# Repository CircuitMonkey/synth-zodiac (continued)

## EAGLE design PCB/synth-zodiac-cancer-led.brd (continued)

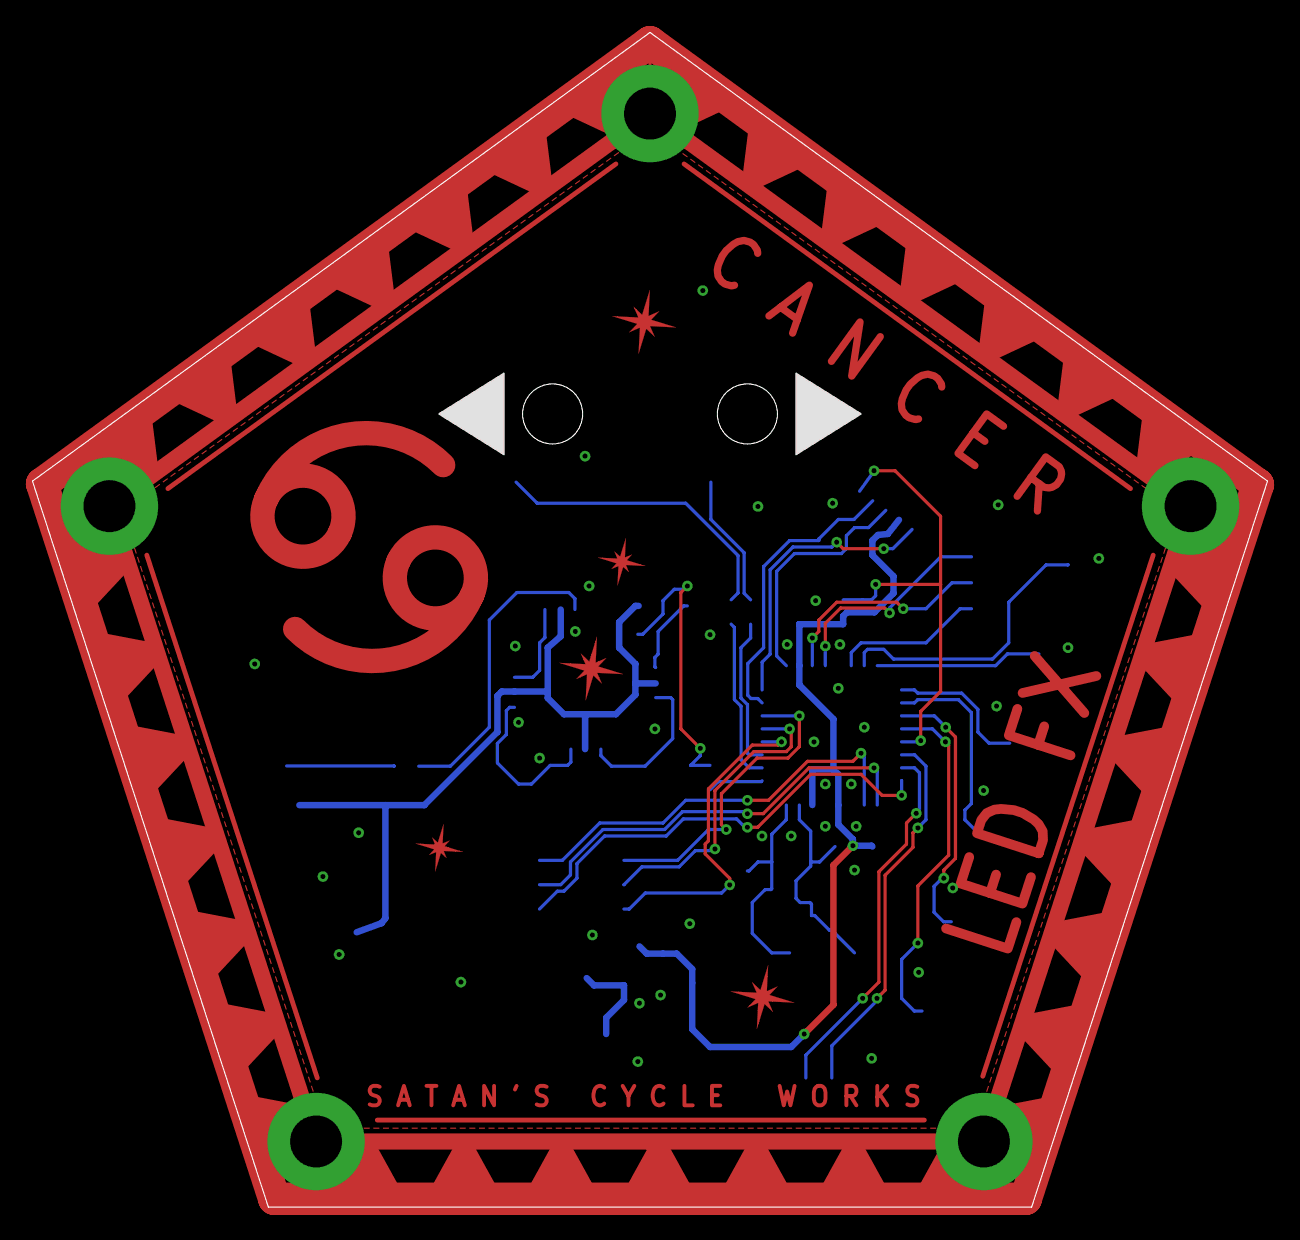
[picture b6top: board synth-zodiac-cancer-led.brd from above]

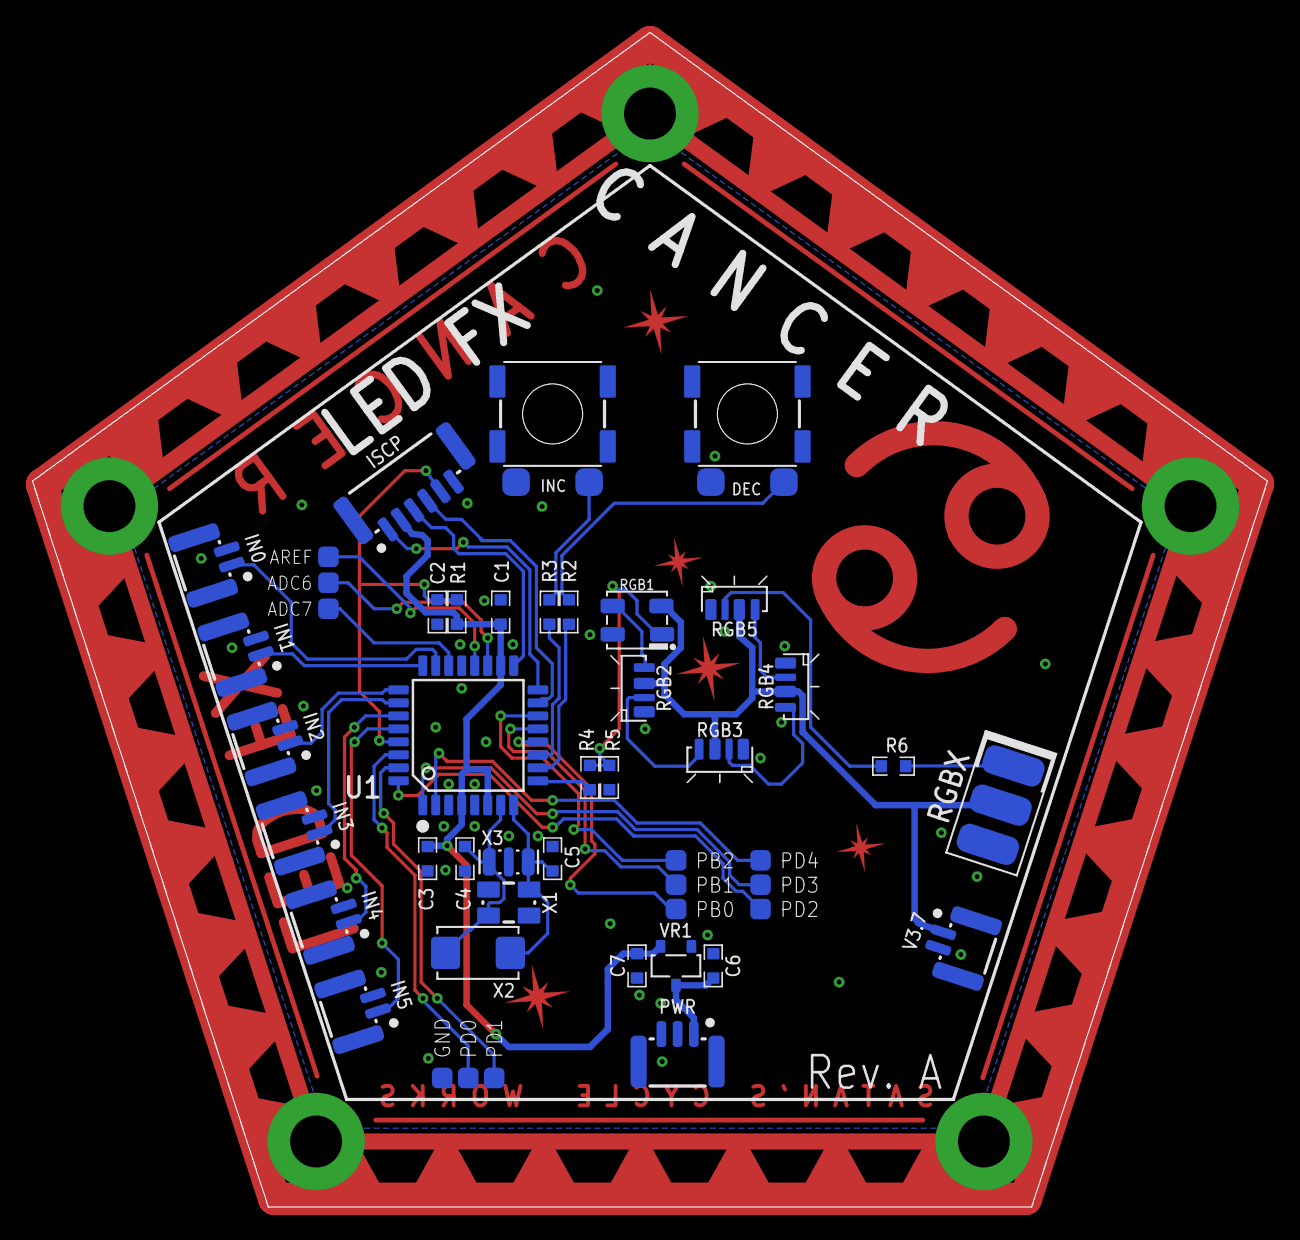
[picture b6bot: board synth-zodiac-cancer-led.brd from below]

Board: 2 copper layers, 76.1 x 72.4 mm, 50 parts (45 on the bottom side), 39 nets.

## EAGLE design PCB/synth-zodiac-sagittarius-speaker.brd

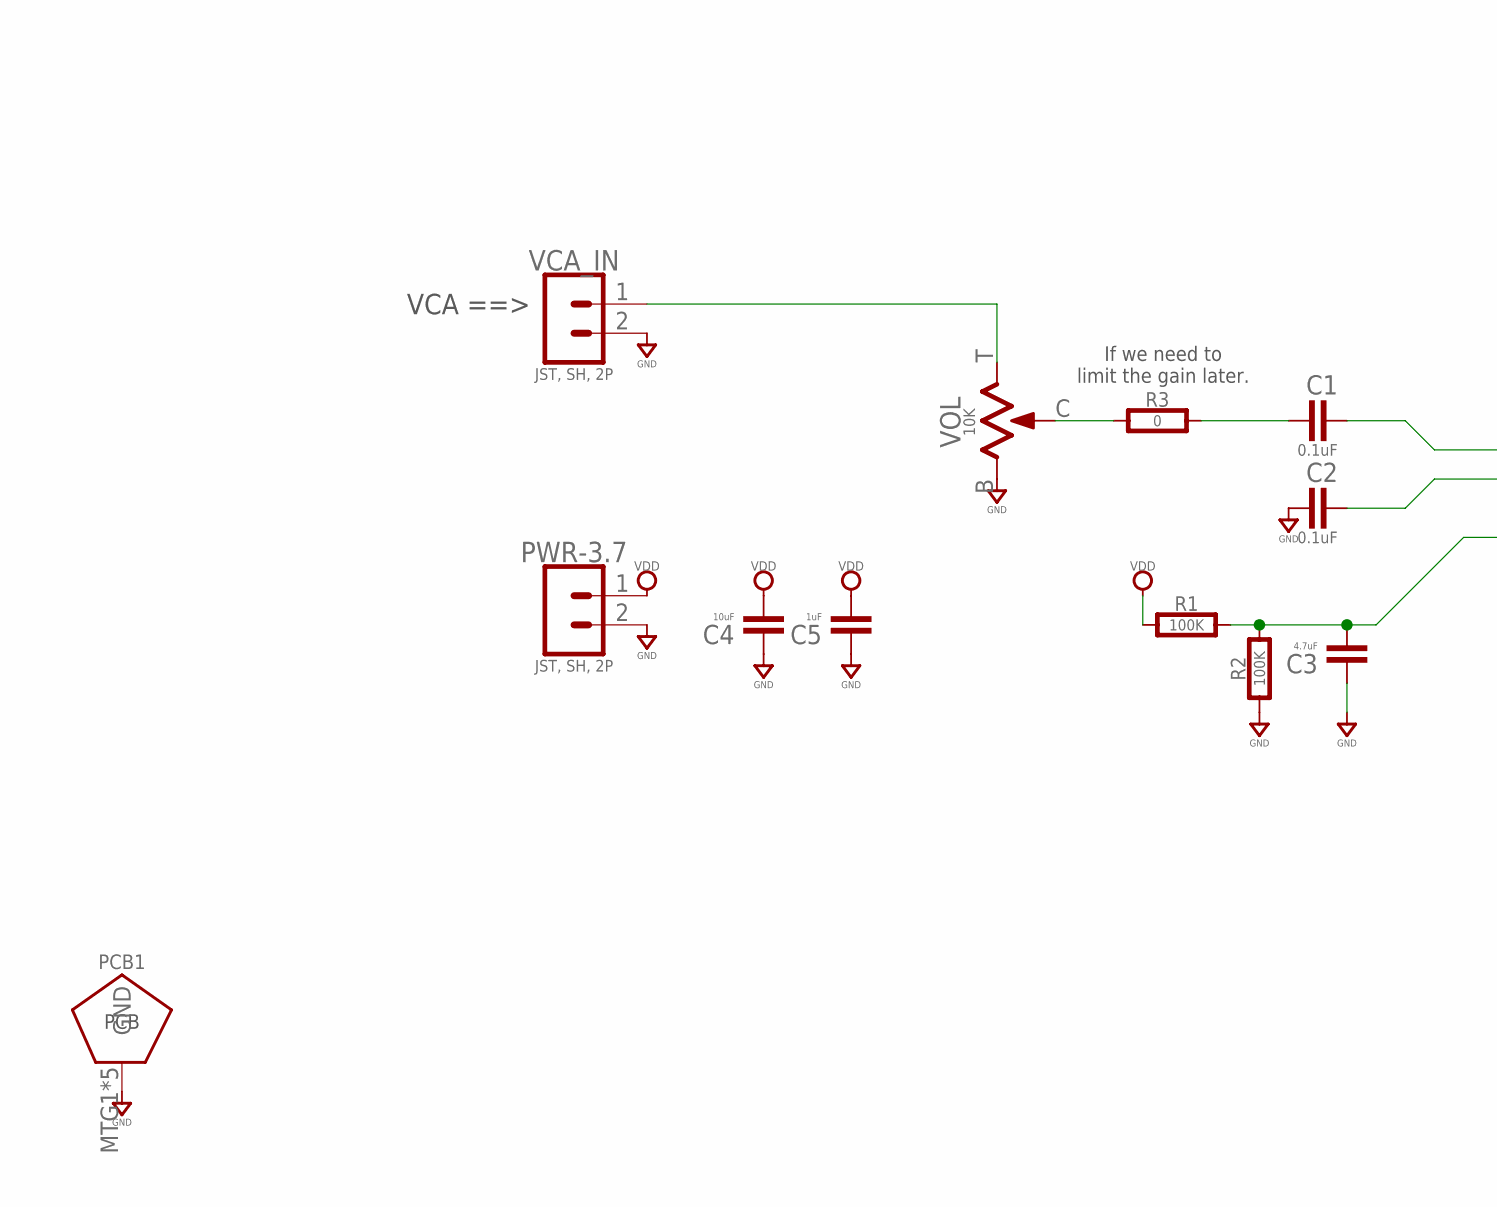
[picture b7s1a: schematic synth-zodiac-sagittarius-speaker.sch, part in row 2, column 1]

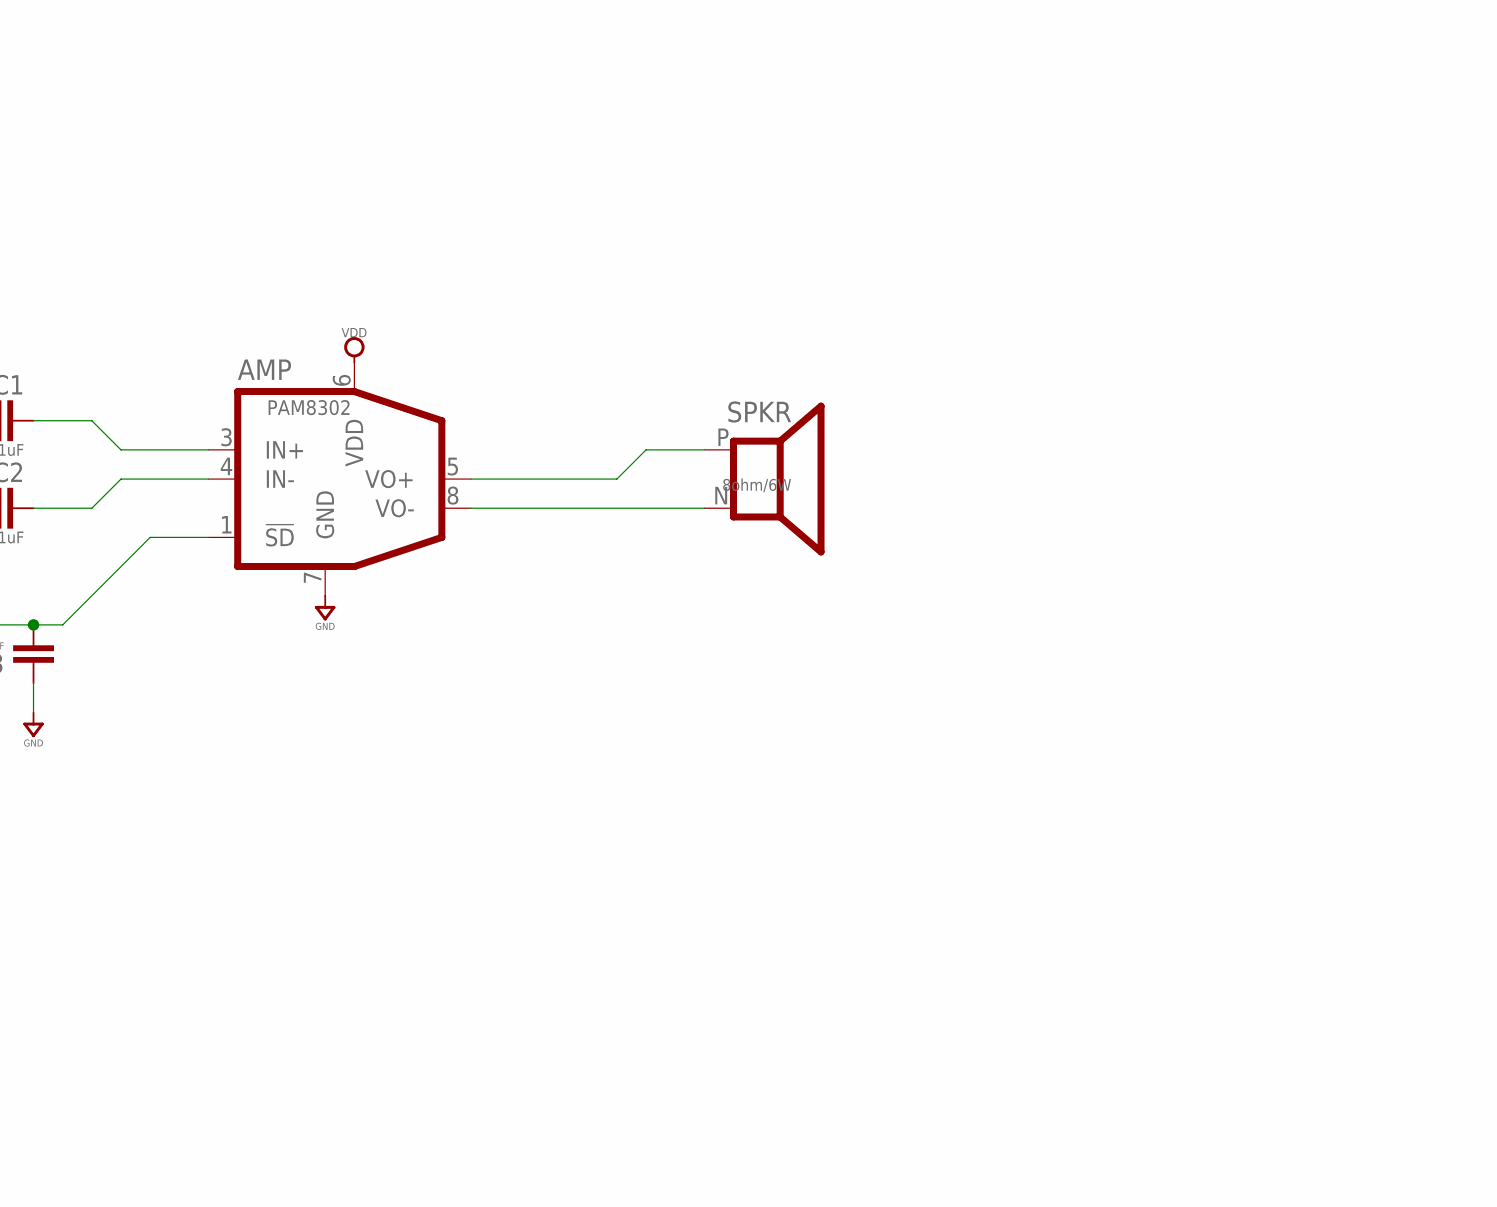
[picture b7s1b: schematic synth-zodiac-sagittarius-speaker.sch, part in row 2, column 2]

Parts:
AMP: PAM8302; U-DFN3030-8
C1, C2: 0.1uF; 0603-CAP
C3: 4.7uF; 0603-CAP
C4: 10uF; 0603-CAP
C5: 1uF; 0603-CAP
PCB1: PCB FAB; PENTAGON-40MM-RAD
PWR-3.7: JST, SH, 2P; BM02B-SRSS-TB
R1, R2: 100K; 0603-RES
R3: 0; 0603-RES
SPKR: 8ohm/6W; SPKR-40X30
VCA_IN: JST, SH, 2P; BM02B-SRSS-TB
VOL: 10K; POT-RV9110

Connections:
GND: AMP.7 (GND), C2.1, C3.1, C4.1, C5.1, PCB1.MTG1, PCB1.MTG2, PCB1.MTG3, PCB1.MTG4, PCB1.MTG5, PWR-3.7.2, R2.1, VCA_IN.2, VOL.B (1)
unnamed: AMP.3 (IN+), C1.2
unnamed: AMP.4 (IN-), C2.2
unnamed: VCA_IN.1, VOL.T (3)
unnamed: C1.1, R3.2
unnamed: AMP.1 (!SD), C3.2, R1.2, R2.2
unnamed: AMP.5 (VO+), SPKR.P (+)
unnamed: AMP.8 (VO-), SPKR.N (-)
unnamed: R3.1, VOL.C (2)
VDD: AMP.6 (VDD), C4.2, C5.2, PWR-3.7.1, R1.1

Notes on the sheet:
VCA ==>
If we need to limit the gain later.
Amp & Speaker
Zodiac Synth
Sagittarius
SATAN'S CYCLE WORKS

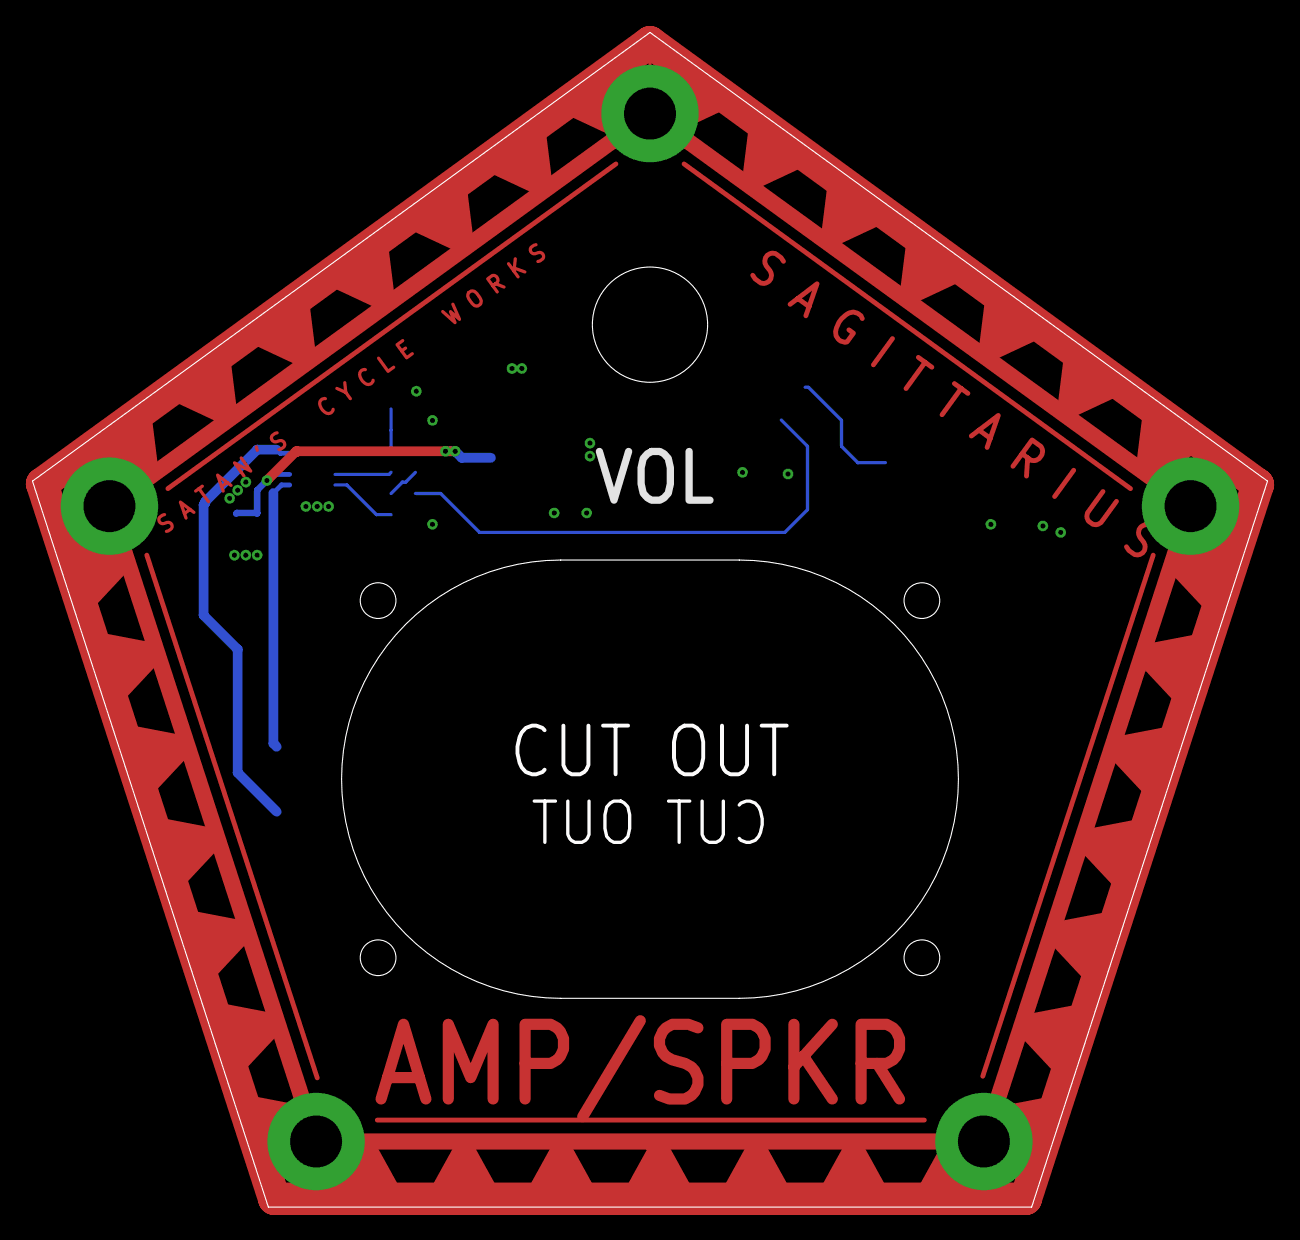
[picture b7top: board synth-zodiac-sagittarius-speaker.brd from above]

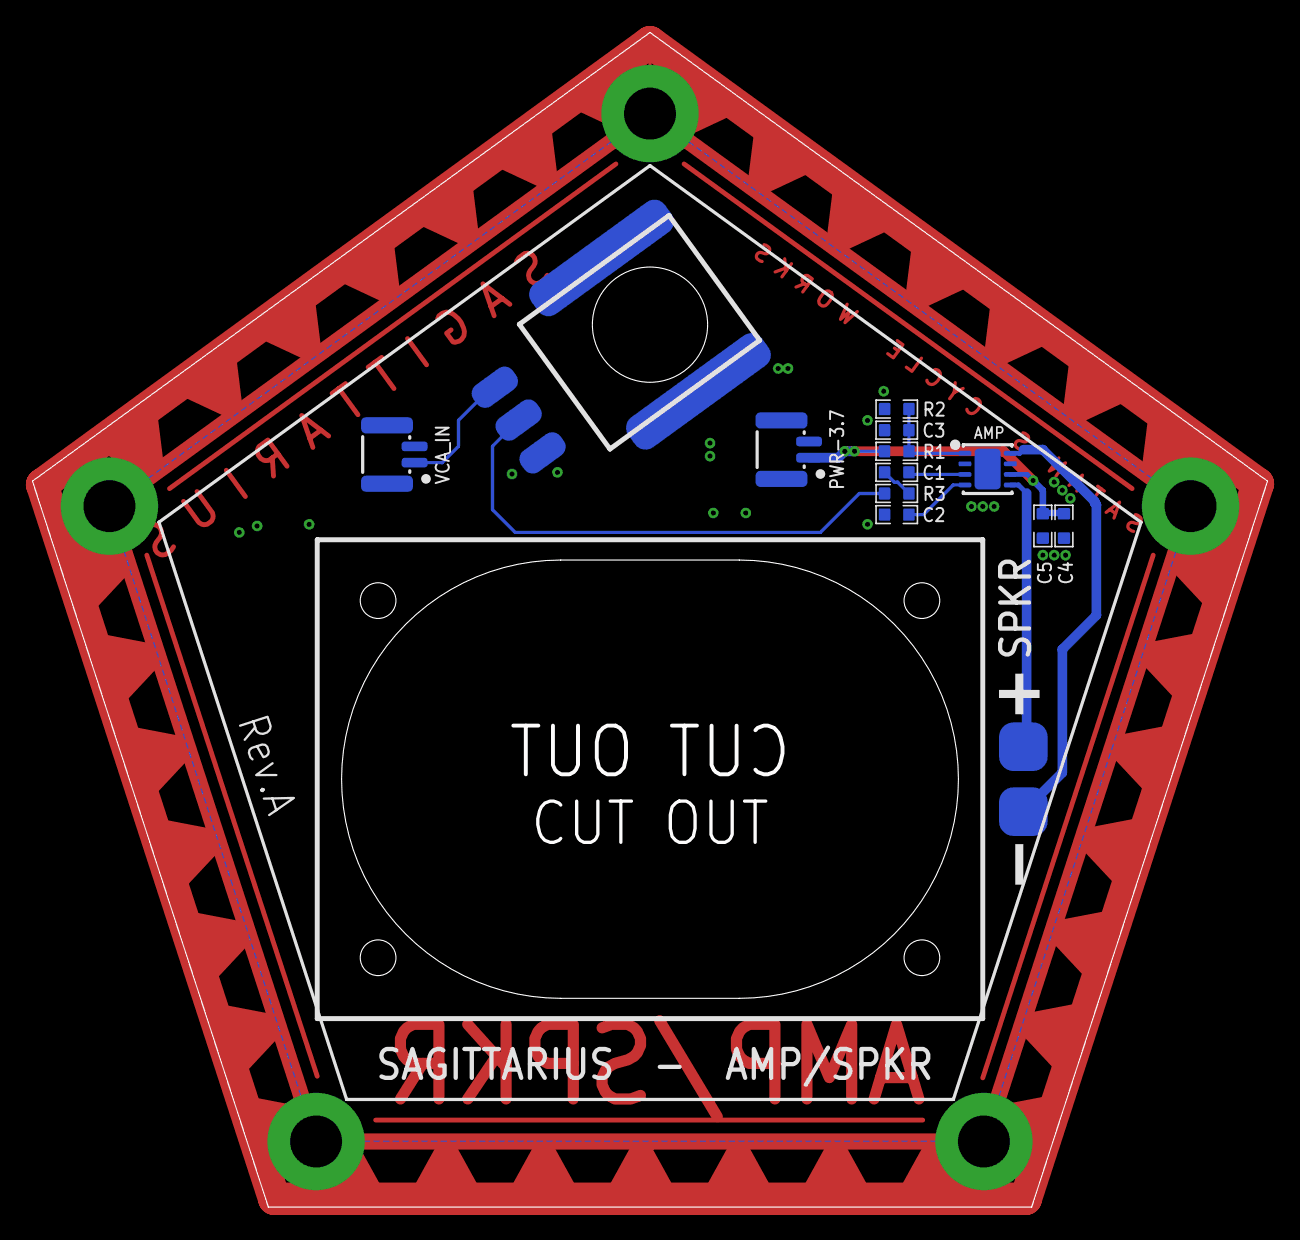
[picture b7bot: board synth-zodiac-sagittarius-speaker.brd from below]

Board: 2 copper layers, 76.1 x 72.4 mm, 14 parts (13 on the bottom side), 10 nets.

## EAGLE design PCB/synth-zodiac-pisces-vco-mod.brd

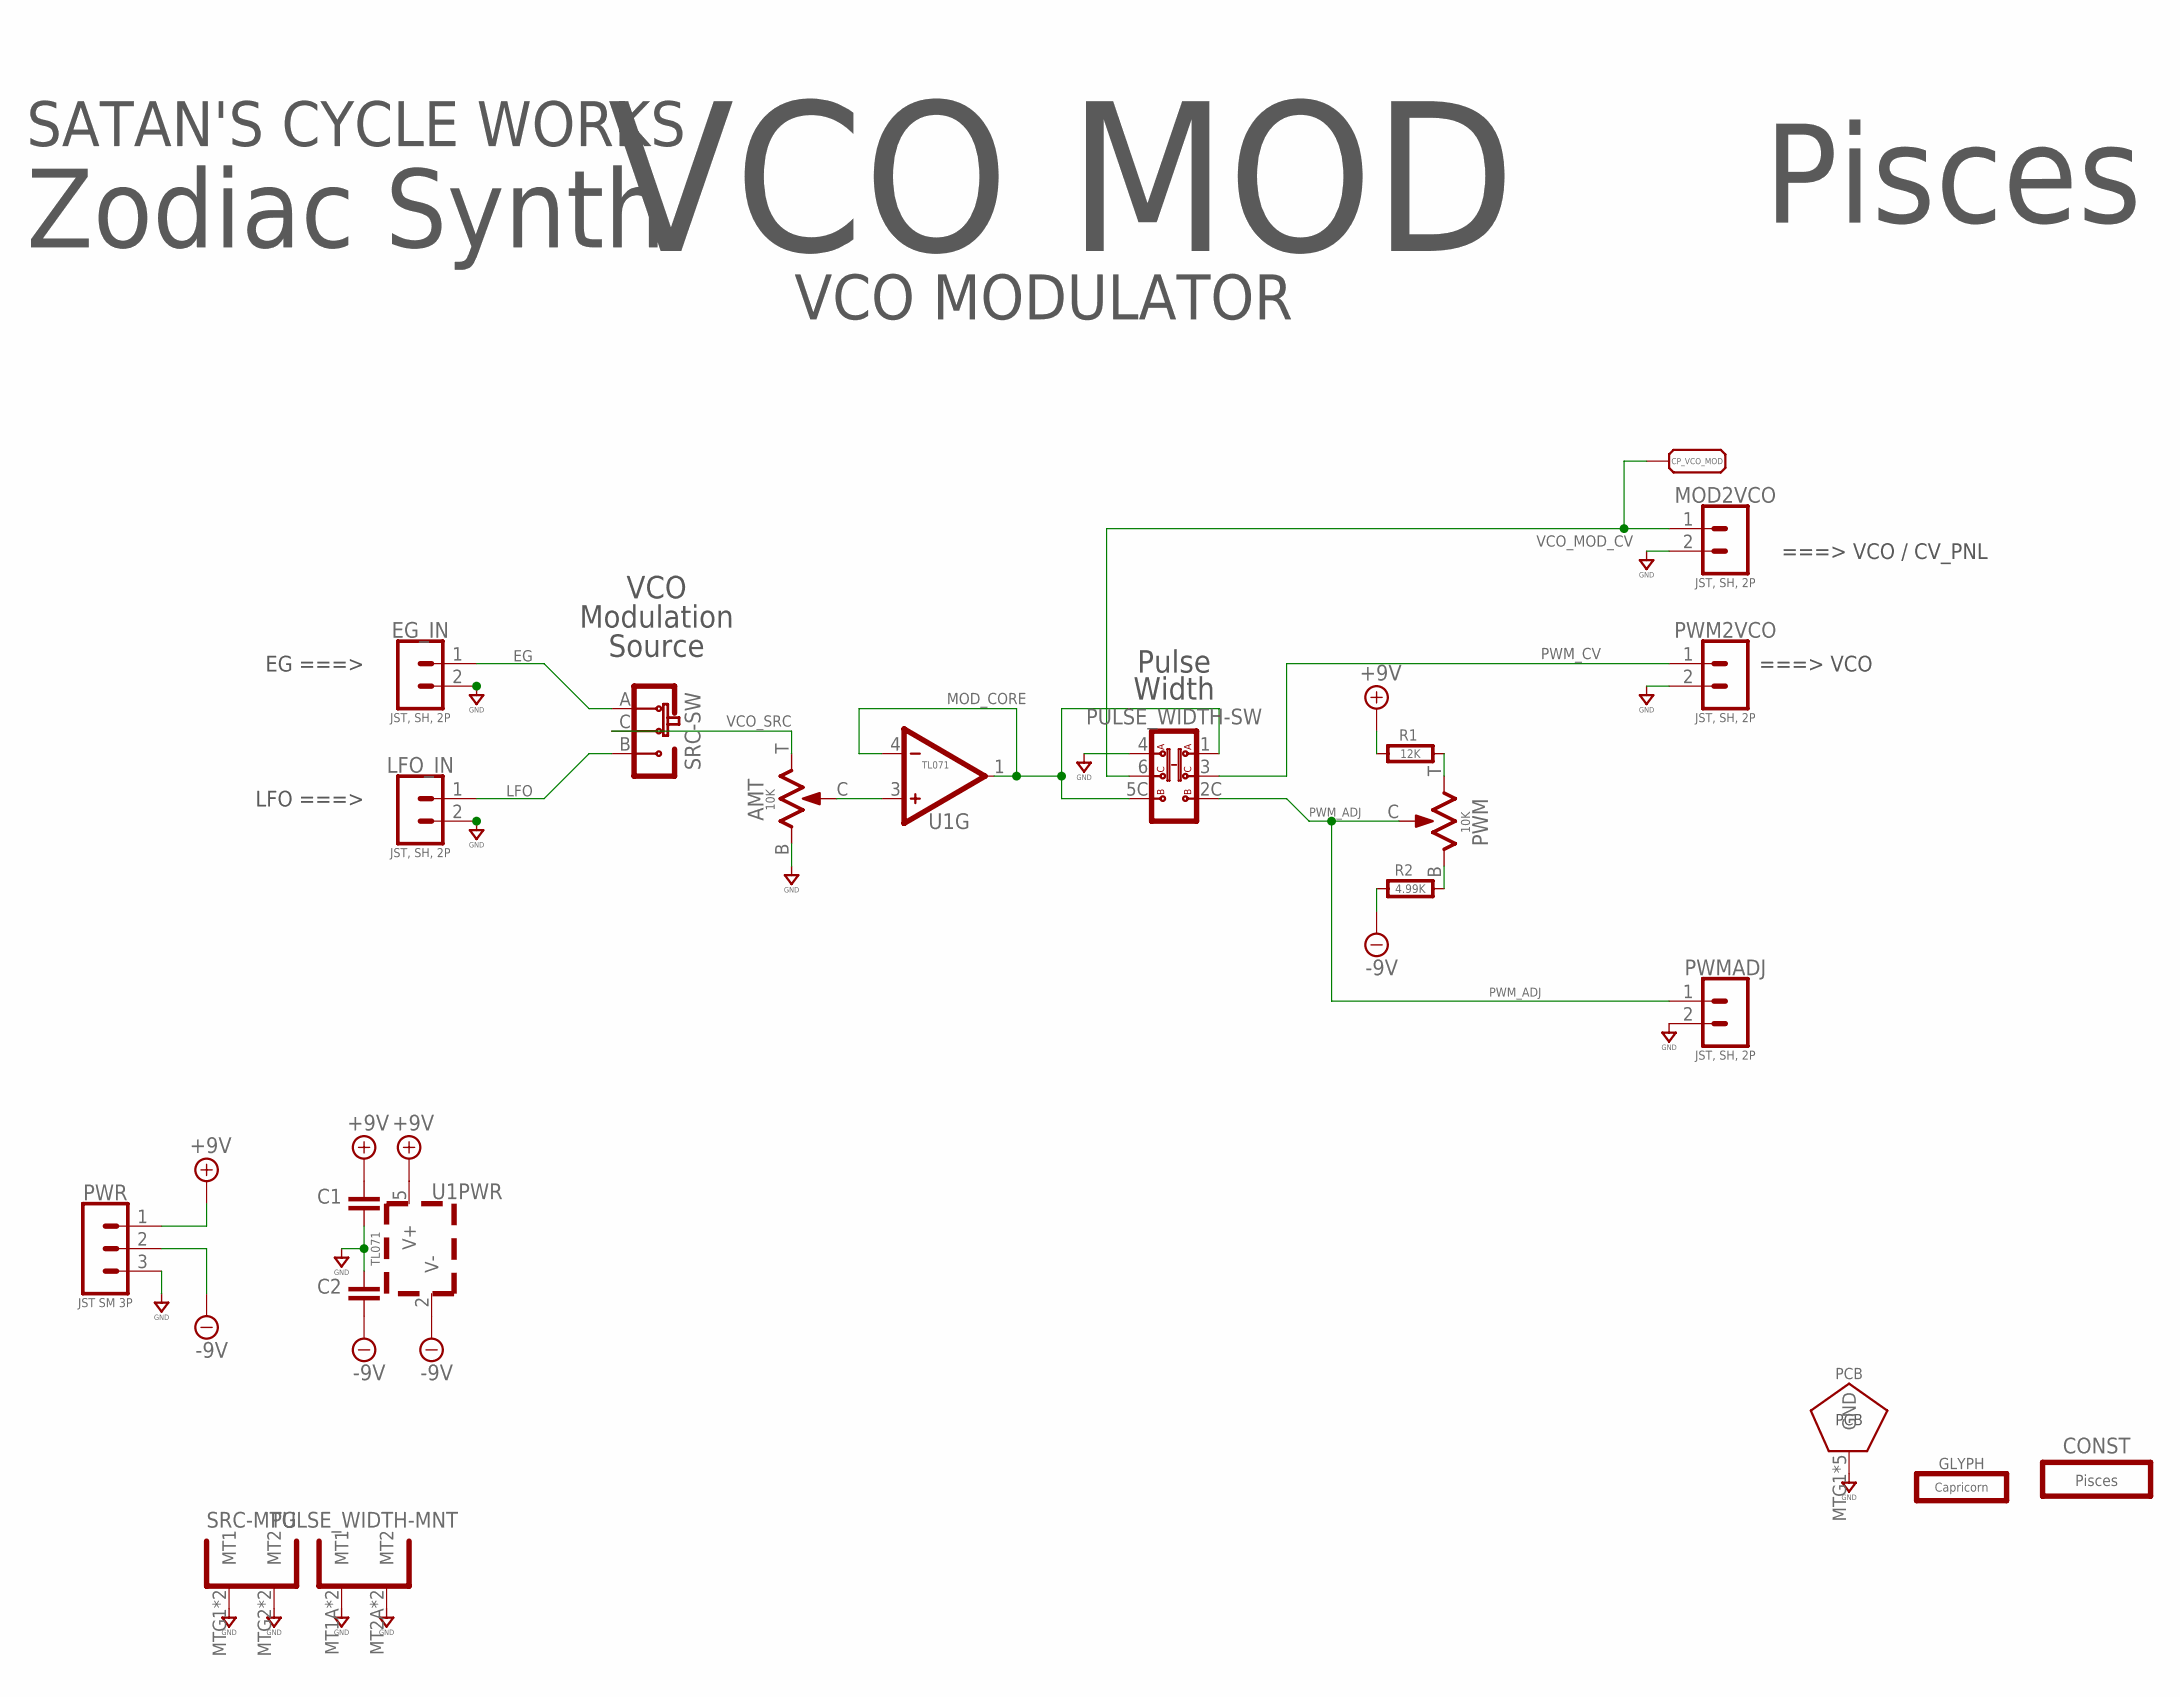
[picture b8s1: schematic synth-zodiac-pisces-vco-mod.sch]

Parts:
AMT: 10K; POT-RV9110
C1, C2: 0.1uF; 0603-CAP
CONST: Pisces; PISCES-CONST
CP_VCO_MOD: PADSMD-070X070; SMD-070MIL
EG_IN: JST, SH, 2P; BM02B-SRSS-TB
GLYPH: Capricorn; CAPRICORN-GLYPH
LFO_IN: JST, SH, 2P; BM02B-SRSS-TB
MOD2VCO: JST, SH, 2P; BM02B-SRSS-TB
PCB: PCB FAB; PENTAGON-40MM-RAD
PULSE_WIDTH: Switch, DPDT; CK_OS202013MT5-PNL-SMT-2
PWM: 10K; POT-RV9110
PWM2VCO: JST, SH, 2P; BM02B-SRSS-TB
PWMADJ: JST, SH, 2P; BM02B-SRSS-TB
PWR: JST SM 3P; BM03B-SRSS-TB
R1: 12K; 0603-RES
R2: 4.99K; 0603-RES
SRC: SLIDE-SPDT-MNTSS-12-F45-TH-PCB-2; SS-12-F45-PNL-SMT-2
U1: TL071; SOT-23-5

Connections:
+9V: C1.1, PWR.1, R1.1, U1.5 (V+)
-9V: C2.2, PWR.2, R2.2, U1.2 (V-)
EG: EG_IN.1, SRC.A
GND: AMT.B (1), C1.2, C2.1, EG_IN.2, LFO_IN.2, MOD2VCO.2, PCB.MTG1, PCB.MTG2, PCB.MTG3, PCB.MTG4, PCB.MTG5, PULSE_WIDTH.4 (2A), PULSE_WIDTH.MT1A (MT1), PULSE_WIDTH.MT2A (MT2), PULSE_WIDTH.MT3A (MT1), PULSE_WIDTH.MT4A (MT2), PWM2VCO.2, PWMADJ.2, PWR.3, SRC.MTG1 (MT1), SRC.MTG2 (MT2), SRC.MTG3 (MT1), SRC.MTG4 (MT2)
LFO: LFO_IN.1, SRC.B
MOD_CORE: PULSE_WIDTH.1 (1A), PULSE_WIDTH.5C (2B), U1.1 (OUT), U1.4 (-)
unnamed: AMT.C (2), U1.3 (+)
unnamed: PWM.B (1), R2.1
unnamed: PWM.T (3), R1.2
PWM_ADJ: PULSE_WIDTH.2C (1B), PWM.C (2), PWMADJ.1
PWM_CV: PULSE_WIDTH.3 (1C), PWM2VCO.1
VCO_MOD_CV: CP_VCO_MOD.1, MOD2VCO.1, PULSE_WIDTH.6 (2C)
VCO_SRC: AMT.T (3), SRC.C

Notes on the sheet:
VCO MODULATOR
VCO Modulation Source
Pulse Width
EG ===>
LFO ===>
===> VCO / CV_PNL
===> VCO
VCO MOD
Zodiac Synth
Pisces
SATAN'S CYCLE WORKS

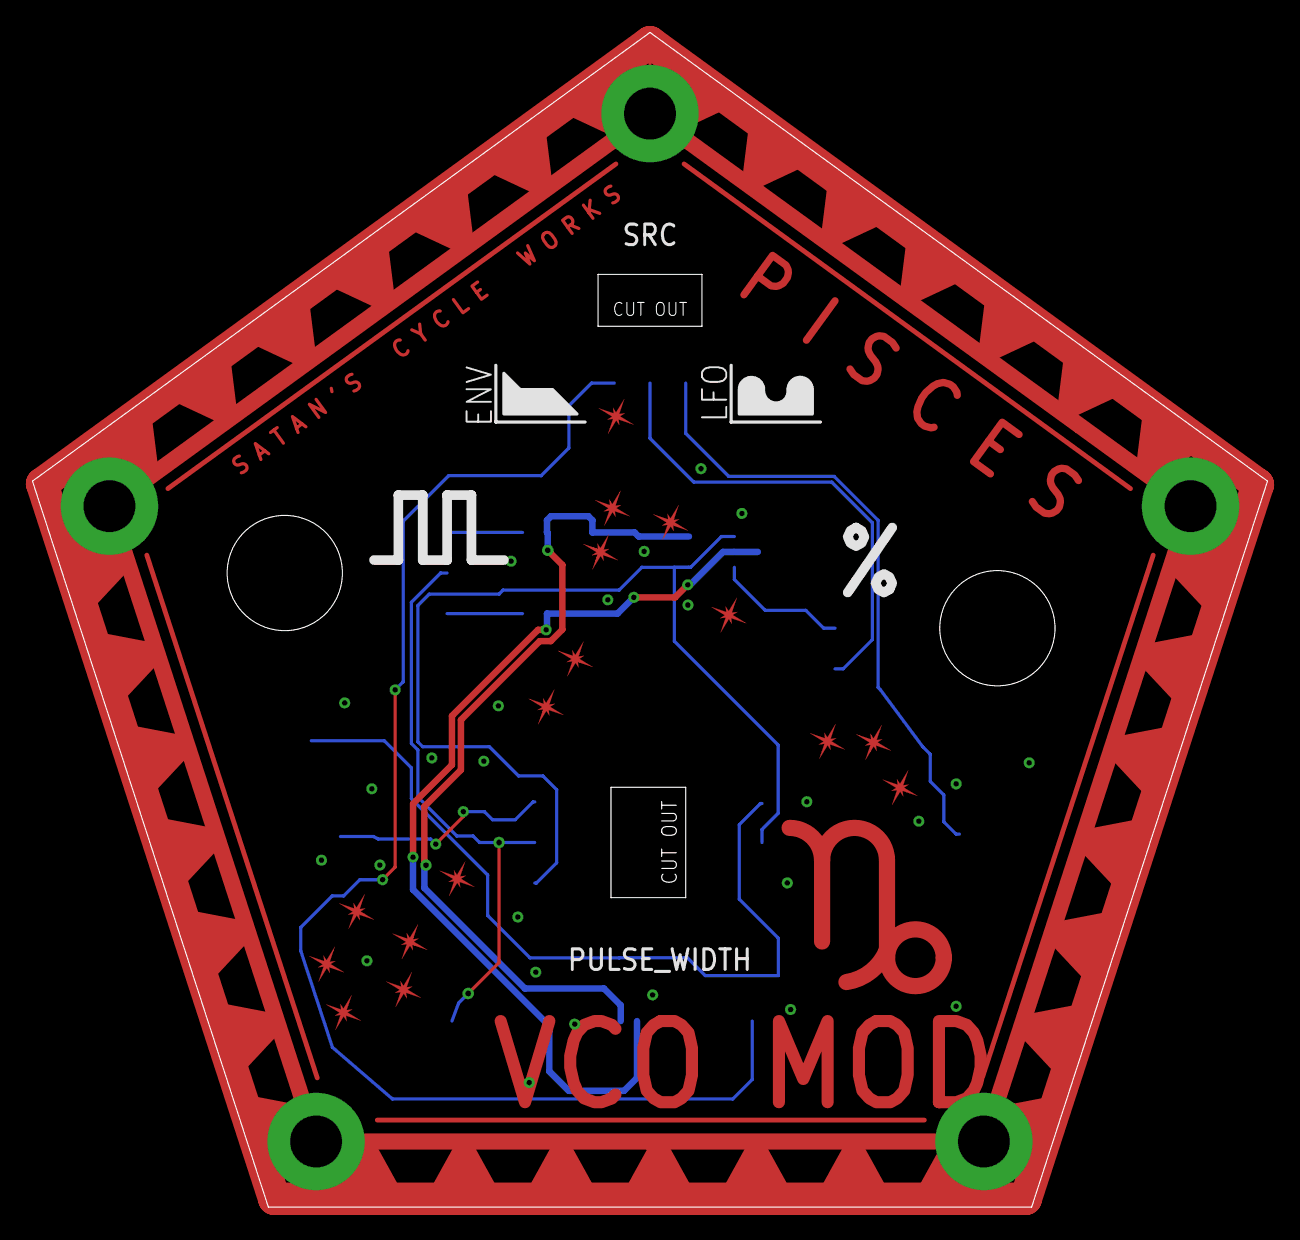
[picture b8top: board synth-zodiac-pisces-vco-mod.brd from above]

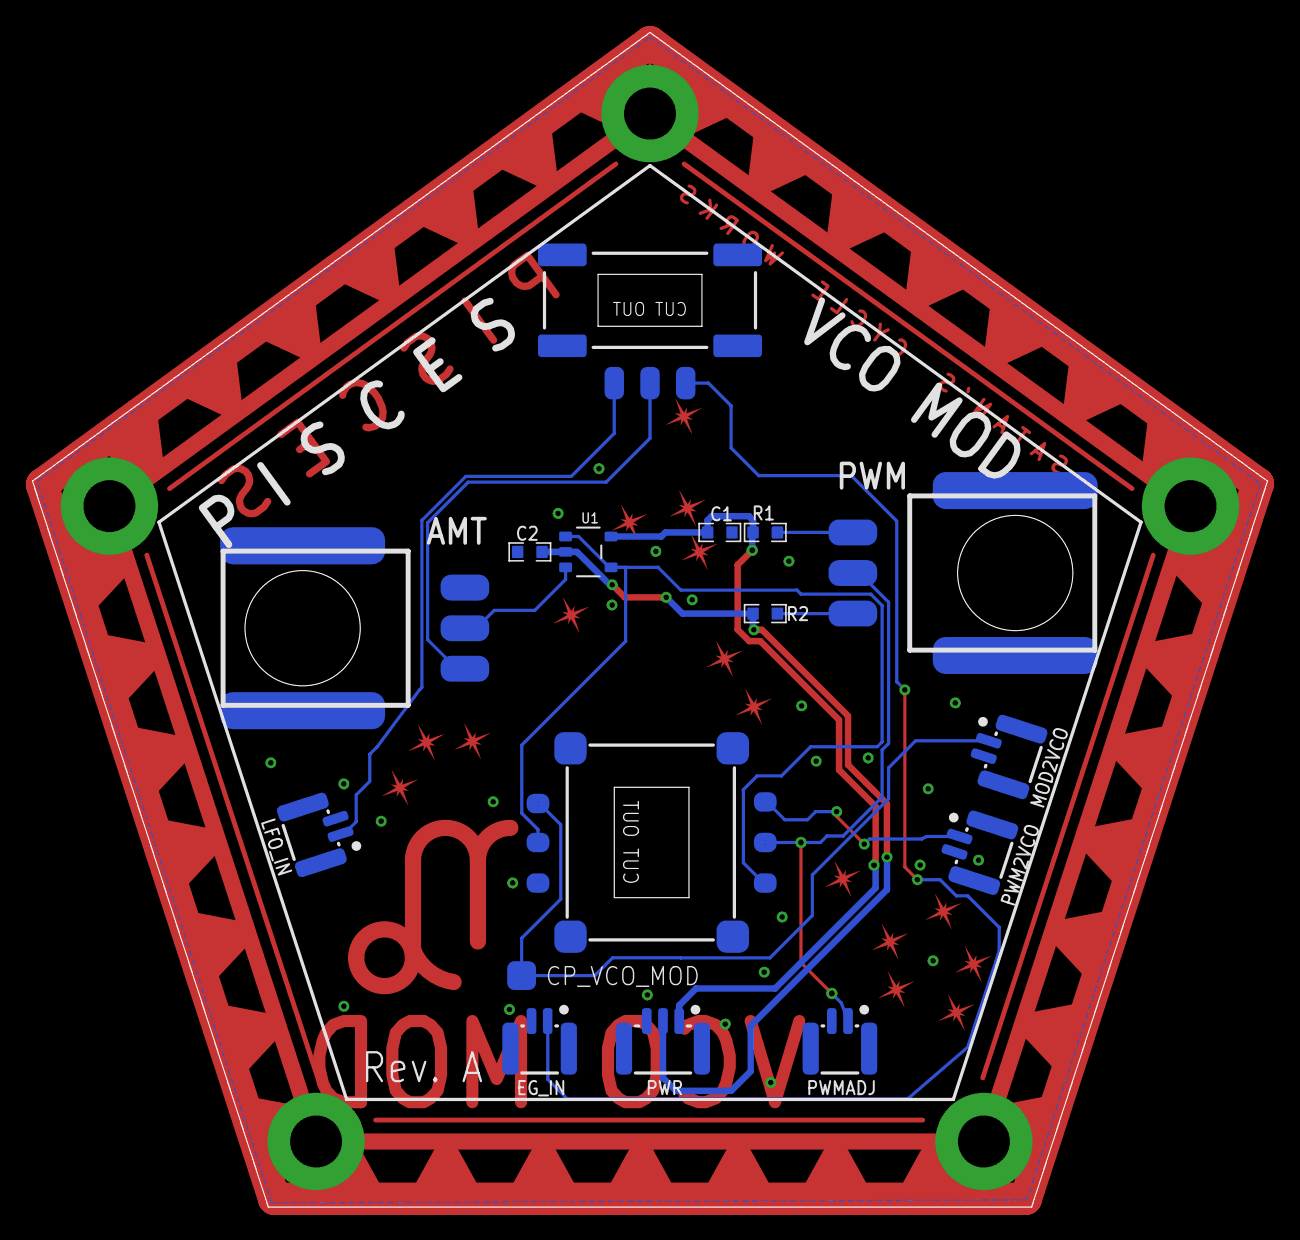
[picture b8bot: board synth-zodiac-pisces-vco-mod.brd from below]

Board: 2 copper layers, 76.0 x 72.3 mm, 19 parts (14 on the bottom side), 13 nets.

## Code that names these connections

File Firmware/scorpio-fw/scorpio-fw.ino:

/**
 * Zodiac Synth - Scorpio - Keyboard Firmware
 *
 *  ATmega328P @16Mhz
 *     Use: "Arduino Nano" device in IDE
 *           New Board Only: Tools -> Burn Bootloader. (sets xtal and fuses)
 *           After:  Sketch -> Upload using Programmer 
 */

#include <Adafruit_NeoPixel.h>
#ifdef __AVR__
 #include <avr/power.h> // Required for 16 MHz Adafruit Trinket
#endif

#define LED_PIN   A4
#define LED_COUNT 1

// Charlie-plex keyboard (row-column array)
// Write High to each column in sequence.
// For each Column(output), read the state of Rows(input)
// Rev. A KBD needs pull-down resistors on R pins!
//
#define R0 A0
#define R1 A1
#define R2 A2
#define R3 A3

#define C0 4
#define C1 5
#define C2 6
#define C3 7

#define NOTE_C  0
#define NOTE_CS 1
#define NOTE_D  2
#define NOTE_DS 3
#define NOTE_E  4
#define NOTE_F  5
#define NOTE_FS 6
#define NOTE_G  7
#define NOTE_GS 8
#define NOTE_A  9
#define NOTE_AS 10
#define NOTE_B  11
#define NOTE_C2 12

// analog(pwm) out
#define KBV 9

#define TRIG 8
#define GATE 10

Adafruit_NeoPixel strip(LED_COUNT, LED_PIN, NEO_GRB + NEO_KHZ800);

int8_t lastKey = -1;

uint8_t col[4] = { C0, C1, C2, C3 };
uint8_t row[4] = { R0, R1, R2, R3 };

// Raw values used for possible calibration.
uint8_t note[16] = {
  0,   // C
  16,  // C#
  32,  // D
  48,  // D#
  64,  // E
  80,  // F
  96,  // F#
  112, // G
  128, // G#
  144, // A
  160, // A#
  176, // B
  192, // C2
  208, // C2#  // Not used.
  224, // D2   // Not used.
  240  // D2#  // Not used.
};

void setup() {
  pinMode(KBV, OUTPUT);
  pinMode(GATE, OUTPUT);
  pinMode(TRIG, OUTPUT);

  digitalWrite(GATE, LOW);
  digitalWrite(TRIG, LOW);

  strip.begin();           // INITIALIZE NeoPixel strip object (REQUIRED)
  strip.show();            // Turn OFF all pixels ASAP
  strip.setBrightness(100); // Set BRIGHTNESS to about 1/5 (max = 255)
  
  colorWipe(strip.Color(255,   0,   0), 1000); // Red
  colorWipe(strip.Color(  0, 255,   0), 1000); // Green
  colorWipe(strip.Color(  0,   0, 255), 1000); // Blue

  pinMode( R0, INPUT );
  pinMode( R1, INPUT );
  pinMode( R2, INPUT );
  pinMode( R3, INPUT );

  pinMode( C0, OUTPUT );
  pinMode( C1, OUTPUT );
  pinMode( C2, OUTPUT );
  pinMode( C3, OUTPUT );
}

void loop() {
  // colorWipe(strip.Color(255,   0,   0), 1000); // Red
  // colorWipe(strip.Color(  0, 255,   0), 1000); // Green
  // colorWipe(strip.Color(  0,   0, 255), 1000); // Blue

  // rainbow(30);             // Flowing rainbow cycle along the whole strip

  // Test KBV output
  // for ( int i=0; i < 256; i++ ) {
  //   analogWrite(KBV, i);
  //   delay(10);
  // }
  
  int8_t n = scanKeys();
  if ( n >=0 && n < 13 ) {
    analogWrite(KBV, note[n]); // Write analog value of note.
    digitalWrite(GATE, HIGH); // Open the gate.
    if ( n != lastKey ) {
      // Trigger pulse
      digitalWrite(TRIG, HIGH);
      delay(10);
      digitalWrite(TRIG, LOW);
      lastKey = n;

      strip.setPixelColor(0,strip.ColorHSV(n * 5461)); // Hue range 0-65535
    }
  } else { // Nothing pressed or user released button.

    // TODO: Decay light brightness.
    
    digitalWrite(GATE, LOW); // Close the gate.
    lastKey = -1;
    strip.setPixelColor(0,strip.Color(0,   0,   0)); // OFF
  }
  strip.show();            // Turn OFF all pixels ASAP
  delay(10);
}

int8_t scanKeys() {
  for ( int i=0; i<4; i++ ) {
    digitalWrite( C0, LOW);
    digitalWrite( C1, LOW);
    digitalWrite( C2, LOW);
    digitalWrite( C3, LOW);
    digitalWrite(col[i], HIGH);

    // Return first pressed key, if any.
    for ( int j=0; j< 4; j++ ) {
      if ( digitalRead(row[j]) == HIGH ) return (j*4)+i; // 0-12
    }
  }

  return -1; // No key pressed.
}

// Fill strip pixels one after another with a color. Strip is NOT cleared
// first; anything there will be covered pixel by pixel. Pass in color
// (as a single 'packed' 32-bit value, which you can get by calling
// strip.Color(red, green, blue) as shown in the loop() function above),
// and a delay time (in milliseconds) between pixels.
void colorWipe(uint32_t color, int wait) {
  for(int i=0; i<strip.numPixels(); i++) { // For each pixel in strip...
    strip.setPixelColor(i, color);         //  Set pixel's color (in RAM)
    strip.show();                          //  Update strip to match
    delay(wait);                           //  Pause for a moment
  }
}

// Rainbow cycle along whole strip. Pass delay time (in ms) between frames.
void rainbow(int wait) {
  // Hue of first pixel runs 5 complete loops through the color wheel.
  // Color wheel has a range of 65536 but it's OK if we roll over, so
  // just count from 0 to 5*65536. Adding 256 to firstPixelHue each time
  // means we'll make 5*65536/256 = 1280 passes through this loop:
  for(long firstPixelHue = 0; firstPixelHue < 5*65536; firstPixelHue += 256) {
    // strip.rainbow() can take a single argument (first pixel hue) or
    // optionally a few extras: number of rainbow repetitions (default 1),
    // saturation and value (brightness) (both 0-255, similar to the
    // ColorHSV() function, default 255), and a true/false flag for whether
    // to apply gamma correction to provide 'truer' colors (default true).
    strip.rainbow(firstPixelHue);
    // Above line is equivalent to:
    // strip.rainbow(firstPixelHue, 1, 255, 255, true);
    strip.show(); // Update strip with new contents
    delay(wait);  // Pause for a moment
  }
}

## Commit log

2022-05-21 Start of four sections.
2022-06-20 Block Diagrams
2022-06-20 Cowbell test board sent to fab.
2022-06-20 Snapshot of designs so far.
2022-06-30 Almost ready for FAB.
    Sagittarius was mis-spelled, renamed it. Taurus is still WIP.
2023-09-08 Work in progress for rev A, VCO rev.B
2023-09-08 VCO Rev. A final
2023-09-08 Archive old version of KBD
2023-09-08 VCO Rev. A documents
2023-11-18 Update and create component test boards
2023-11-18 Various board updates.
2023-12-11 Perhaps final Rev. A?
2023-12-23 Clean up example layout images.
2023-12-23 Gerbers as FABed 12-2023.
2024-01-21 Tune values and some schematic visual tweaks.
2024-01-21 Bill of Materials spreadsheets added.
2024-01-21 VCO BOM and schematic
2024-01-21 Photos of work in progress.
2024-01-21 Firmware for some boards.
2024-01-21 Schematic for VCO Rev.b
2024-01-27 Update component value for charging rate.
2024-01-27 Brighter and a little faster color cycle.
2024-01-27 Basic keyboard code. Needs testing.
